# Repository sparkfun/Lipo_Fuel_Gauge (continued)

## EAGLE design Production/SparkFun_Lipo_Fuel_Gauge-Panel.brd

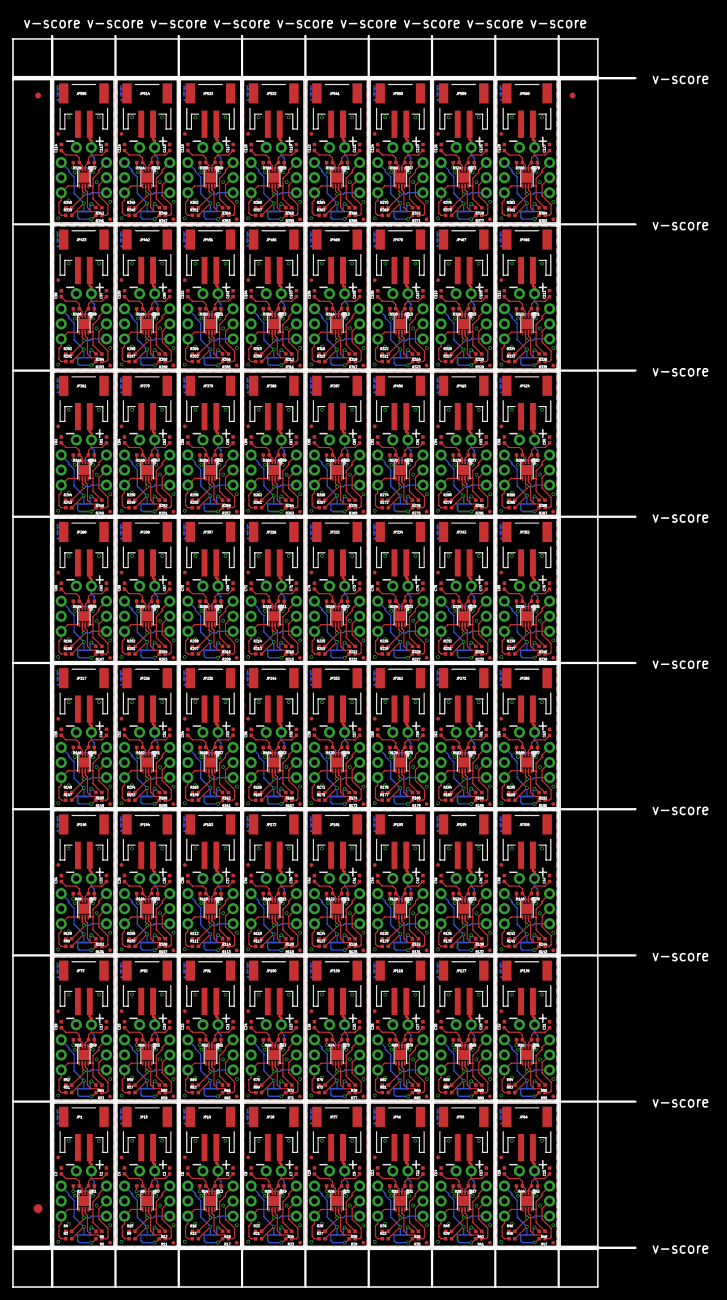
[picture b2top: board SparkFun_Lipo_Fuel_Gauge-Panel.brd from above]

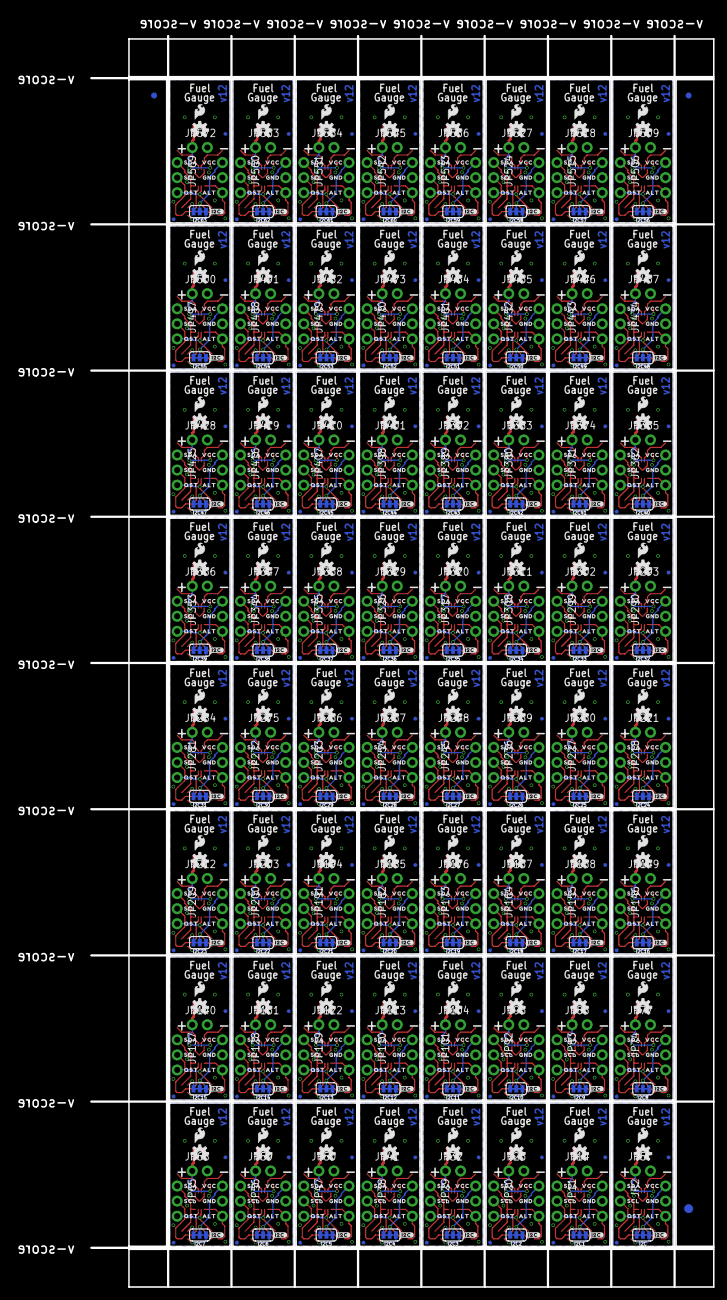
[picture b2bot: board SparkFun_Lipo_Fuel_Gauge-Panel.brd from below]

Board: 2 copper layers, 104.9 x 210.8 mm, 1798 parts (963 on the bottom side), 704 nets.

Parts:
C1, C3, C5, C7, C9, C11, C13, C15, C17, C19, C21, C23, C25, C27, C29, C31, C33, C35, C37, C39, C41, C43, C45, C47, C49, C51, C53, C55, C57, C59, C61, C63, C65, C67, C69, C71, C73, C75, C77, C79, C81, C83, C85, C87, C89, C91, C93, C95, C97, C99, C101, C103, C105, C107, C109, C111, C113, C115, C117, C119, C121, C123, C125, C127: 1.0uF; 0402-TIGHT
C2, C4, C6, C8, C10, C12, C14, C16, C18, C20, C22, C24, C26, C28, C30, C32, C34, C36, C38, C40, C42, C44, C46, C48, C50, C52, C54, C56, C58, C60, C62, C64, C66, C68, C70, C72, C74, C76, C78, C80, C82, C84, C86, C88, C90, C92, C94, C96, C98, C100, C102, C104, C106, C108, C110, C112, C114, C116, C118, C120, C122, C124, C126, C128: 10nF; 0402-TIGHT
E$1, E$2, E$3, E$4: FIDUCIAL-1X2
E$5, E$6: FIDUCIAL-1.5X3
I2C, I2C1, I2C2, I2C3, I2C4, I2C5, I2C6, I2C7, I2C8, I2C9, I2C10, I2C11, I2C12, I2C13, I2C14, I2C15, I2C16, I2C17, I2C18, I2C19, I2C20, I2C21, I2C22, I2C23, I2C24, I2C25, I2C26, I2C27, I2C28, I2C29, I2C30, I2C31, I2C32, I2C33, I2C34, I2C35, I2C36, I2C37, I2C38, I2C39, I2C40, I2C41, I2C42, I2C43, I2C44, I2C45, I2C46, I2C47, I2C48, I2C49, I2C50, I2C51, I2C52, I2C53, I2C54, I2C55, I2C56, I2C57, I2C58, I2C59, I2C60, I2C61, I2C62, I2C63: JUMPER-SMT_3_2-NC_TRACE_SILK; SMT-JUMPER_3_2-NC_TRACE_SILK
JP1, JP10, JP19, JP28, JP37, JP46, JP55, JP64, JP73, JP82, JP91, JP100, JP109, JP118, JP127, JP136, JP145, JP154, JP163, JP172, JP181, JP190, JP199, JP208, JP217, JP226, JP235, JP244, JP253, JP262, JP271, JP280, JP289, JP298, JP307, JP316, JP325, JP334, JP343, JP352, JP361, JP370, JP379, JP388, JP397, JP406, JP415, JP424, JP433, JP442, JP451, JP460, JP469, JP478, JP487, JP496, JP505, JP514, JP523, JP532, JP541, JP550, JP559, JP568: input; JST-2-SMD
JP2, JP4, JP11, JP12, JP20, JP21, JP29, JP30, JP38, JP39, JP47, JP48, JP56, JP57, JP65, JP66, JP74, JP75, JP83, JP84, JP92, JP93, JP101, JP102, JP110, JP111, JP119, JP120, JP128, JP129, JP137, JP138, JP146, JP147, JP155, JP156, JP164, JP165, JP173, JP174, JP182, JP183, JP191, JP192, JP200, JP201, JP209, JP210, JP218, JP219, JP227, JP228, JP236, JP237, JP245, JP246, JP254, JP255, JP263, JP264, JP272, JP273, JP281, JP282, JP290, JP291, JP299, JP300, JP308, JP309, JP317, JP318, JP326, JP327, JP335, JP336, JP344, JP345, JP353, JP354, JP362, JP363, JP371, JP372, JP380, JP381, JP389, JP390, JP398, JP399, JP407, JP408, JP416, JP417, JP425, JP426, JP434, JP435, JP443, JP444, JP452, JP453, JP461, JP462, JP470, JP471, JP479, JP480, JP488, JP489, JP497, JP498, JP506, JP507, JP515, JP516, JP524, JP525, JP533, JP534, JP542, JP543, JP551, JP552, JP560, JP561, JP569, JP570: 1X03_NO_SILK
JP3, JP13, JP22, JP31, JP40, JP49, JP58, JP67, JP76, JP85, JP94, JP103, JP112, JP121, JP130, JP139, JP148, JP157, JP166, JP175, JP184, JP193, JP202, JP211, JP220, JP229, JP238, JP247, JP256, JP265, JP274, JP283, JP292, JP301, JP310, JP319, JP328, JP337, JP346, JP355, JP364, JP373, JP382, JP391, JP400, JP409, JP418, JP427, JP436, JP445, JP454, JP463, JP472, JP481, JP490, JP499, JP508, JP517, JP526, JP535, JP544, JP553, JP562, JP571: SFE_LOGO_FLAME.1_INCH; SFE_LOGO_FLAME_.1
JP5, JP14, JP23, JP32, JP41, JP50, JP59, JP68, JP77, JP86, JP95, JP104, JP113, JP122, JP131, JP140, JP149, JP158, JP167, JP176, JP185, JP194, JP203, JP212, JP221, JP230, JP239, JP248, JP257, JP266, JP275, JP284, JP293, JP302, JP311, JP320, JP329, JP338, JP347, JP356, JP365, JP374, JP383, JP392, JP401, JP410, JP419, JP428, JP437, JP446, JP455, JP464, JP473, JP482, JP491, JP500, JP509, JP518, JP527, JP536, JP545, JP554, JP563, JP572: 1X02_NO_SILK
JP6, JP7, JP8, JP9, JP15, JP16, JP17, JP18, JP24, JP25, JP26, JP27, JP33, JP34, JP35, JP36, JP42, JP43, JP44, JP45, JP51, JP52, JP53, JP54, JP60, JP61, JP62, JP63, JP69, JP70, JP71, JP72, JP78, JP79, JP80, JP81, JP87, JP88, JP89, JP90, JP96, JP97, JP98, JP99, JP105, JP106, JP107, JP108, JP114, JP115, JP116, JP117, JP123, JP124, JP125, JP126, JP132, JP133, JP134, JP135, JP141, JP142, JP143, JP144, JP150, JP151, JP152, JP153, JP159, JP160, JP161, JP162, JP168, JP169, JP170, JP171, JP177, JP178, JP179, JP180, JP186, JP187, JP188, JP189, JP195, JP196, JP197, JP198, JP204, JP205, JP206, JP207, JP213, JP214, JP215, JP216, JP222, JP223, JP224, JP225, JP231, JP232, JP233, JP234, JP240, JP241, JP242, JP243, JP249, JP250, JP251, JP252, JP258, JP259, JP260, JP261, JP267, JP268, JP269, JP270, JP276, JP277, JP278, JP279, JP285, JP286, JP287, JP288, JP294, JP295, JP296, JP297, JP303, JP304, JP305, JP306, JP312, JP313, JP314, JP315, JP321, JP322, JP323, JP324, JP330, JP331, JP332, JP333, JP339, JP340, JP341, JP342, JP348, JP349, JP350, JP351, JP357, JP358, JP359, JP360, JP366, JP367, JP368, JP369, JP375, JP376, JP377, JP378, JP384, JP385, JP386, JP387, JP393, JP394, JP395, JP396, JP402, JP403, JP404, JP405, JP411, JP412, JP413, JP414, JP420, JP421, JP422, JP423, JP429, JP430, JP431, JP432, JP438, JP439, JP440, JP441, JP447, JP448, JP449, JP450, JP456, JP457, JP458, JP459, JP465, JP466, JP467, JP468, JP474, JP475, JP476, JP477, JP483, JP484, JP485, JP486, JP492, JP493, JP494, JP495, JP501, JP502, JP503, JP504, JP510, JP511, JP512, JP513, JP519, JP520, JP521, JP522, JP528, JP529, JP530, JP531, JP537, JP538, JP539, JP540, JP546, JP547, JP548, JP549, JP555, JP556, JP557, JP558, JP564, JP565, JP566, JP567, JP573, JP574, JP575, JP576: FIDUCIALUFIDUCIAL; FIDUCIAL-MICRO
LOGO1, LOGO2, LOGO3, LOGO4, LOGO5, LOGO6, LOGO7, LOGO8, LOGO9, LOGO10, LOGO11, LOGO12, LOGO13, LOGO14, LOGO15, LOGO16, LOGO17, LOGO18, LOGO19, LOGO20, LOGO21, LOGO22, LOGO23, LOGO24, LOGO25, LOGO26, LOGO27, LOGO28, LOGO29, LOGO30, LOGO31, LOGO32, LOGO33, LOGO34, LOGO35, LOGO36, LOGO37, LOGO38, LOGO39, LOGO40, LOGO41, LOGO42, LOGO43, LOGO44, LOGO45, LOGO46, LOGO47, LOGO48, LOGO49, LOGO50, LOGO51, LOGO52, LOGO53, LOGO54, LOGO55, LOGO56, LOGO57, LOGO58, LOGO59, LOGO60, LOGO61, LOGO62, LOGO63, LOGO64: SFE_LOGO_NAME_FLAMEBLANK; BLANK
R1, R7, R13, R19, R25, R31, R37, R43, R49, R55, R61, R67, R73, R79, R85, R91, R97, R103, R109, R115, R121, R127, R133, R139, R145, R151, R157, R163, R169, R175, R181, R187, R193, R199, R205, R211, R217, R223, R229, R235, R241, R247, R253, R259, R265, R271, R277, R283, R289, R295, R301, R307, R313, R319, R325, R331, R337, R343, R349, R355, R361, R367, R373, R379: 1k; 0402-TIGHT
R2, R8, R14, R20, R26, R32, R38, R44, R50, R56, R62, R68, R74, R80, R86, R92, R98, R104, R110, R116, R122, R128, R134, R140, R146, R152, R158, R164, R170, R176, R182, R188, R194, R200, R206, R212, R218, R224, R230, R236, R242, R248, R254, R260, R266, R272, R278, R284, R290, R296, R302, R308, R314, R320, R326, R332, R338, R344, R350, R356, R362, R368, R374, R380: 100; 0402-TIGHT
R3, R4, R5, R6, R9, R10, R11, R12, R15, R16, R17, R18, R21, R22, R23, R24, R27, R28, R29, R30, R33, R34, R35, R36, R39, R40, R41, R42, R45, R46, R47, R48, R51, R52, R53, R54, R57, R58, R59, R60, R63, R64, R65, R66, R69, R70, R71, R72, R75, R76, R77, R78, R81, R82, R83, R84, R87, R88, R89, R90, R93, R94, R95, R96, R99, R100, R101, R102, R105, R106, R107, R108, R111, R112, R113, R114, R117, R118, R119, R120, R123, R124, R125, R126, R129, R130, R131, R132, R135, R136, R137, R138, R141, R142, R143, R144, R147, R148, R149, R150, R153, R154, R155, R156, R159, R160, R161, R162, R165, R166, R167, R168, R171, R172, R173, R174, R177, R178, R179, R180, R183, R184, R185, R186, R189, R190, R191, R192, R195, R196, R197, R198, R201, R202, R203, R204, R207, R208, R209, R210, R213, R214, R215, R216, R219, R220, R221, R222, R225, R226, R227, R228, R231, R232, R233, R234, R237, R238, R239, R240, R243, R244, R245, R246, R249, R250, R251, R252, R255, R256, R257, R258, R261, R262, R263, R264, R267, R268, R269, R270, R273, R274, R275, R276, R279, R280, R281, R282, R285, R286, R287, R288, R291, R292, R293, R294, R297, R298, R299, R300, R303, R304, R305, R306, R309, R310, R311, R312, R315, R316, R317, R318, R321, R322, R323, R324, R327, R328, R329, R330, R333, R334, R335, R336, R339, R340, R341, R342, R345, R346, R347, R348, R351, R352, R353, R354, R357, R358, R359, R360, R363, R364, R365, R366, R369, R370, R371, R372, R375, R376, R377, R378, R381, R382, R383, R384: 2.2k; 0402-TIGHT
U1, U2, U3, U4, U5, U6, U7, U8, U9, U10, U11, U12, U13, U14, U15, U16, U17, U18, U19, U20, U21, U22, U23, U24, U25, U26, U27, U28, U29, U30, U31, U32, U33, U34, U35, U36, U37, U38, U39, U40, U41, U42, U43, U44, U45, U46, U47, U48, U49, U50, U51, U52, U53, U54, U55, U56, U57, U58, U59, U60, U61, U62, U63, U64: MAX1704X; TDFN-8
U$1, U$9, U$17, U$25, U$33, U$41, U$49, U$57, U$65, U$73, U$81, U$89, U$97, U$105, U$113, U$121, U$129, U$137, U$145, U$153, U$161, U$169, U$177, U$185, U$193, U$201, U$209, U$217, U$225, U$233, U$241, U$249, U$257, U$265, U$273, U$281, U$289, U$297, U$305, U$313, U$321, U$329, U$337, U$345, U$353, U$361, U$369, U$377, U$385, U$393, U$401, U$409, U$417, U$425, U$433, U$441, U$449, U$457, U$465, U$473, U$481, U$489, U$497, U$505: OSHW-LOGOS; OSHW-LOGO-S
U$2, U$11, U$19, U$27, U$35, U$43, U$51, U$59, U$67, U$75, U$83, U$91, U$99, U$107, U$115, U$123, U$131, U$139, U$147, U$155, U$163, U$171, U$179, U$187, U$195, U$203, U$211, U$219, U$227, U$235, U$243, U$251, U$259, U$267, U$275, U$283, U$291, U$299, U$307, U$315, U$323, U$331, U$339, U$347, U$355, U$363, U$371, U$379, U$387, U$395, U$403, U$411, U$419, U$427, U$435, U$443, U$451, U$459, U$467, U$475, U$483, U$491, U$499, U$507: SDA0
U$3, U$12, U$20, U$28, U$36, U$44, U$52, U$60, U$68, U$76, U$84, U$92, U$100, U$108, U$116, U$124, U$132, U$140, U$148, U$156, U$164, U$172, U$180, U$188, U$196, U$204, U$212, U$220, U$228, U$236, U$244, U$252, U$260, U$268, U$276, U$284, U$292, U$300, U$308, U$316, U$324, U$332, U$340, U$348, U$356, U$364, U$372, U$380, U$388, U$396, U$404, U$412, U$420, U$428, U$436, U$444, U$452, U$460, U$468, U$476, U$484, U$492, U$500, U$508: SCL0
U$4, U$13, U$21, U$29, U$37, U$45, U$53, U$61, U$69, U$77, U$85, U$93, U$101, U$109, U$117, U$125, U$133, U$141, U$149, U$157, U$165, U$173, U$181, U$189, U$197, U$205, U$213, U$221, U$229, U$237, U$245, U$253, U$261, U$269, U$277, U$285, U$293, U$301, U$309, U$317, U$325, U$333, U$341, U$349, U$357, U$365, U$373, U$381, U$389, U$397, U$405, U$413, U$421, U$429, U$437, U$445, U$453, U$461, U$469, U$477, U$485, U$493, U$501, U$509: QST0
U$5, U$14, U$22, U$30, U$38, U$46, U$54, U$62, U$70, U$78, U$86, U$94, U$102, U$110, U$118, U$126, U$134, U$142, U$150, U$158, U$166, U$174, U$182, U$190, U$198, U$206, U$214, U$222, U$230, U$238, U$246, U$254, U$262, U$270, U$278, U$286, U$294, U$302, U$310, U$318, U$326, U$334, U$342, U$350, U$358, U$366, U$374, U$382, U$390, U$398, U$406, U$414, U$422, U$430, U$438, U$446, U$454, U$462, U$470, U$478, U$486, U$494, U$502, U$510: VCC0
U$6, U$15, U$23, U$31, U$39, U$47, U$55, U$63, U$71, U$79, U$87, U$95, U$103, U$111, U$119, U$127, U$135, U$143, U$151, U$159, U$167, U$175, U$183, U$191, U$199, U$207, U$215, U$223, U$231, U$239, U$247, U$255, U$263, U$271, U$279, U$287, U$295, U$303, U$311, U$319, U$327, U$335, U$343, U$351, U$359, U$367, U$375, U$383, U$391, U$399, U$407, U$415, U$423, U$431, U$439, U$447, U$455, U$463, U$471, U$479, U$487, U$495, U$503, U$511: GND0
U$7, U$16, U$24, U$32, U$40, U$48, U$56, U$64, U$72, U$80, U$88, U$96, U$104, U$112, U$120, U$128, U$136, U$144, U$152, U$160, U$168, U$176, U$184, U$192, U$200, U$208, U$216, U$224, U$232, U$240, U$248, U$256, U$264, U$272, U$280, U$288, U$296, U$304, U$312, U$320, U$328, U$336, U$344, U$352, U$360, U$368, U$376, U$384, U$392, U$400, U$408, U$416, U$424, U$432, U$440, U$448, U$456, U$464, U$472, U$480, U$488, U$496, U$504, U$512: ALT0
U$8, U$10, U$18, U$26, U$34, U$42, U$50, U$58, U$66, U$74, U$82, U$90, U$98, U$106, U$114, U$122, U$130, U$138, U$146, U$154, U$162, U$170, U$178, U$186, U$194, U$202, U$210, U$218, U$226, U$234, U$242, U$250, U$258, U$266, U$274, U$282, U$290, U$298, U$306, U$314, U$322, U$330, U$338, U$346, U$354, U$362, U$370, U$378, U$386, U$394, U$402, U$410, U$418, U$426, U$434, U$442, U$450, U$458, U$466, U$474, U$482, U$490, U$498, U$506: #I2C#0

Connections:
ALT: JP4.3, R3.1, U2.5
ALT1: JP12.3, R9.1, U1.5
ALT2: JP21.3, R15.1, U3.5
ALT3: JP30.3, R21.1, U4.5
ALT4: JP39.3, R27.1, U5.5
ALT5: JP48.3, R33.1, U6.5
ALT6: JP57.3, R39.1, U7.5
ALT7: JP66.3, R45.1, U8.5
ALT8: JP75.3, R51.1, U9.5
ALT9: JP84.3, R57.1, U10.5
ALT10: JP93.3, R63.1, U11.5
ALT11: JP102.3, R69.1, U12.5
ALT12: JP111.3, R75.1, U13.5
ALT13: JP120.3, R81.1, U14.5
ALT14: JP129.3, R87.1, U15.5
ALT15: JP138.3, R93.1, U16.5
ALT16: JP147.3, R99.1, U17.5
ALT17: JP156.3, R105.1, U18.5
ALT18: JP165.3, R111.1, U19.5
ALT19: JP174.3, R117.1, U20.5
ALT20: JP183.3, R123.1, U21.5
ALT21: JP192.3, R129.1, U22.5
ALT22: JP201.3, R135.1, U23.5
ALT23: JP210.3, R141.1, U24.5
ALT24: JP219.3, R147.1, U25.5
ALT25: JP228.3, R153.1, U26.5
ALT26: JP237.3, R159.1, U27.5
ALT27: JP246.3, R165.1, U28.5
ALT28: JP255.3, R171.1, U29.5
ALT29: JP264.3, R177.1, U30.5
ALT30: JP273.3, R183.1, U31.5
ALT31: JP282.3, R189.1, U32.5
ALT32: JP291.3, R195.1, U33.5
ALT33: JP300.3, R201.1, U34.5
ALT34: JP309.3, R207.1, U35.5
ALT35: JP318.3, R213.1, U36.5
ALT36: JP327.3, R219.1, U37.5
ALT37: JP336.3, R225.1, U38.5
ALT38: JP345.3, R231.1, U39.5
ALT39: JP354.3, R237.1, U40.5
ALT40: JP363.3, R243.1, U41.5
ALT41: JP372.3, R249.1, U42.5
ALT42: JP381.3, R255.1, U43.5
ALT43: JP390.3, R261.1, U44.5
ALT44: JP399.3, R267.1, U45.5
ALT45: JP408.3, R273.1, U46.5
ALT46: JP417.3, R279.1, U47.5
ALT47: JP426.3, R285.1, U48.5
ALT48: JP435.3, R291.1, U49.5
ALT49: JP444.3, R297.1, U50.5
ALT50: JP453.3, R303.1, U51.5
ALT51: JP462.3, R309.1, U52.5
ALT52: JP471.3, R315.1, U53.5
ALT53: JP480.3, R321.1, U54.5
ALT54: JP489.3, R327.1, U55.5
ALT55: JP498.3, R333.1, U56.5
ALT56: JP507.3, R339.1, U57.5
ALT57: JP516.3, R345.1, U58.5
ALT58: JP525.3, R351.1, U59.5
ALT59: JP534.3, R357.1, U60.5
ALT60: JP543.3, R363.1, U61.5
ALT61: JP552.3, R369.1, U62.5
ALT62: JP561.3, R375.1, U63.5
ALT63: JP570.3, R381.1, U64.5
GND: C1.2, C2.2, JP1.1, JP4.2, JP5.2, R4.1, U2.1, U2.4, U2.EP
GND1: C3.2, C4.2, JP10.1, JP12.2, JP14.2, R10.1, U1.1, U1.4, U1.EP
GND2: C5.2, C6.2, JP19.1, JP21.2, JP23.2, R16.1, U3.1, U3.4, U3.EP
GND3: C7.2, C8.2, JP28.1, JP30.2, JP32.2, R22.1, U4.1, U4.4, U4.EP
GND4: C9.2, C10.2, JP37.1, JP39.2, JP41.2, R28.1, U5.1, U5.4, U5.EP
GND5: C11.2, C12.2, JP46.1, JP48.2, JP50.2, R34.1, U6.1, U6.4, U6.EP
GND6: C13.2, C14.2, JP55.1, JP57.2, JP59.2, R40.1, U7.1, U7.4, U7.EP
GND7: C15.2, C16.2, JP64.1, JP66.2, JP68.2, R46.1, U8.1, U8.4, U8.EP
GND8: C17.2, C18.2, JP73.1, JP75.2, JP77.2, R52.1, U9.1, U9.4, U9.EP
GND9: C19.2, C20.2, JP82.1, JP84.2, JP86.2, R58.1, U10.1, U10.4, U10.EP
GND10: C21.2, C22.2, JP91.1, JP93.2, JP95.2, R64.1, U11.1, U11.4, U11.EP
GND11: C23.2, C24.2, JP100.1, JP102.2, JP104.2, R70.1, U12.1, U12.4, U12.EP
GND12: C25.2, C26.2, JP109.1, JP111.2, JP113.2, R76.1, U13.1, U13.4, U13.EP
GND13: C27.2, C28.2, JP118.1, JP120.2, JP122.2, R82.1, U14.1, U14.4, U14.EP
GND14: C29.2, C30.2, JP127.1, JP129.2, JP131.2, R88.1, U15.1, U15.4, U15.EP
GND15: C31.2, C32.2, JP136.1, JP138.2, JP140.2, R94.1, U16.1, U16.4, U16.EP
GND16: C33.2, C34.2, JP145.1, JP147.2, JP149.2, R100.1, U17.1, U17.4, U17.EP
GND17: C35.2, C36.2, JP154.1, JP156.2, JP158.2, R106.1, U18.1, U18.4, U18.EP
GND18: C37.2, C38.2, JP163.1, JP165.2, JP167.2, R112.1, U19.1, U19.4, U19.EP
GND19: C39.2, C40.2, JP172.1, JP174.2, JP176.2, R118.1, U20.1, U20.4, U20.EP
GND20: C41.2, C42.2, JP181.1, JP183.2, JP185.2, R124.1, U21.1, U21.4, U21.EP
GND21: C43.2, C44.2, JP190.1, JP192.2, JP194.2, R130.1, U22.1, U22.4, U22.EP
GND22: C45.2, C46.2, JP199.1, JP201.2, JP203.2, R136.1, U23.1, U23.4, U23.EP
GND23: C47.2, C48.2, JP208.1, JP210.2, JP212.2, R142.1, U24.1, U24.4, U24.EP
GND24: C49.2, C50.2, JP217.1, JP219.2, JP221.2, R148.1, U25.1, U25.4, U25.EP
GND25: C51.2, C52.2, JP226.1, JP228.2, JP230.2, R154.1, U26.1, U26.4, U26.EP
GND26: C53.2, C54.2, JP235.1, JP237.2, JP239.2, R160.1, U27.1, U27.4, U27.EP
GND27: C55.2, C56.2, JP244.1, JP246.2, JP248.2, R166.1, U28.1, U28.4, U28.EP
GND28: C57.2, C58.2, JP253.1, JP255.2, JP257.2, R172.1, U29.1, U29.4, U29.EP
GND29: C59.2, C60.2, JP262.1, JP264.2, JP266.2, R178.1, U30.1, U30.4, U30.EP
GND30: C61.2, C62.2, JP271.1, JP273.2, JP275.2, R184.1, U31.1, U31.4, U31.EP
GND31: C63.2, C64.2, JP280.1, JP282.2, JP284.2, R190.1, U32.1, U32.4, U32.EP
GND32: C65.2, C66.2, JP289.1, JP291.2, JP293.2, R196.1, U33.1, U33.4, U33.EP
GND33: C67.2, C68.2, JP298.1, JP300.2, JP302.2, R202.1, U34.1, U34.4, U34.EP
GND34: C69.2, C70.2, JP307.1, JP309.2, JP311.2, R208.1, U35.1, U35.4, U35.EP
GND35: C71.2, C72.2, JP316.1, JP318.2, JP320.2, R214.1, U36.1, U36.4, U36.EP
GND36: C73.2, C74.2, JP325.1, JP327.2, JP329.2, R220.1, U37.1, U37.4, U37.EP
GND37: C75.2, C76.2, JP334.1, JP336.2, JP338.2, R226.1, U38.1, U38.4, U38.EP
GND38: C77.2, C78.2, JP343.1, JP345.2, JP347.2, R232.1, U39.1, U39.4, U39.EP
GND39: C79.2, C80.2, JP352.1, JP354.2, JP356.2, R238.1, U40.1, U40.4, U40.EP
GND40: C81.2, C82.2, JP361.1, JP363.2, JP365.2, R244.1, U41.1, U41.4, U41.EP
GND41: C83.2, C84.2, JP370.1, JP372.2, JP374.2, R250.1, U42.1, U42.4, U42.EP
GND42: C85.2, C86.2, JP379.1, JP381.2, JP383.2, R256.1, U43.1, U43.4, U43.EP
GND43: C87.2, C88.2, JP388.1, JP390.2, JP392.2, R262.1, U44.1, U44.4, U44.EP
GND44: C89.2, C90.2, JP397.1, JP399.2, JP401.2, R268.1, U45.1, U45.4, U45.EP
GND45: C91.2, C92.2, JP406.1, JP408.2, JP410.2, R274.1, U46.1, U46.4, U46.EP
GND46: C93.2, C94.2, JP415.1, JP417.2, JP419.2, R280.1, U47.1, U47.4, U47.EP
GND47: C95.2, C96.2, JP424.1, JP426.2, JP428.2, R286.1, U48.1, U48.4, U48.EP
GND48: C97.2, C98.2, JP433.1, JP435.2, JP437.2, R292.1, U49.1, U49.4, U49.EP
GND49: C99.2, C100.2, JP442.1, JP444.2, JP446.2, R298.1, U50.1, U50.4, U50.EP
GND50: C101.2, C102.2, JP451.1, JP453.2, JP455.2, R304.1, U51.1, U51.4, U51.EP
GND51: C103.2, C104.2, JP460.1, JP462.2, JP464.2, R310.1, U52.1, U52.4, U52.EP
GND52: C105.2, C106.2, JP469.1, JP471.2, JP473.2, R316.1, U53.1, U53.4, U53.EP
GND53: C107.2, C108.2, JP478.1, JP480.2, JP482.2, R322.1, U54.1, U54.4, U54.EP
GND54: C109.2, C110.2, JP487.1, JP489.2, JP491.2, R328.1, U55.1, U55.4, U55.EP
GND55: C111.2, C112.2, JP496.1, JP498.2, JP500.2, R334.1, U56.1, U56.4, U56.EP
GND56: C113.2, C114.2, JP505.1, JP507.2, JP509.2, R340.1, U57.1, U57.4, U57.EP
GND57: C115.2, C116.2, JP514.1, JP516.2, JP518.2, R346.1, U58.1, U58.4, U58.EP
GND58: C117.2, C118.2, JP523.1, JP525.2, JP527.2, R352.1, U59.1, U59.4, U59.EP
GND59: C119.2, C120.2, JP532.1, JP534.2, JP536.2, R358.1, U60.1, U60.4, U60.EP
GND60: C121.2, C122.2, JP541.1, JP543.2, JP545.2, R364.1, U61.1, U61.4, U61.EP
GND61: C123.2, C124.2, JP550.1, JP552.2, JP554.2, R370.1, U62.1, U62.4, U62.EP
GND62: C125.2, C126.2, JP559.1, JP561.2, JP563.2, R376.1, U63.1, U63.4, U63.EP
GND63: C127.2, C128.2, JP568.1, JP570.2, JP572.2, R382.1, U64.1, U64.4, U64.EP
unnamed: I2C.3, R6.2
unnamed: C1.1, R1.2, U2.2
unnamed: I2C.1, R5.2
unnamed: C3.1, R7.2, U1.2
unnamed: I2C1.3, R12.2
unnamed: I2C1.1, R11.2
unnamed: C5.1, R13.2, U3.2
unnamed: I2C2.3, R18.2
unnamed: I2C2.1, R17.2
unnamed: C7.1, R19.2, U4.2
unnamed: I2C3.3, R24.2
unnamed: I2C3.1, R23.2
unnamed: C9.1, R25.2, U5.2
unnamed: I2C4.3, R30.2
unnamed: I2C4.1, R29.2
unnamed: C11.1, R31.2, U6.2
unnamed: I2C5.3, R36.2
unnamed: I2C5.1, R35.2
unnamed: C13.1, R37.2, U7.2
unnamed: I2C6.3, R42.2
unnamed: I2C6.1, R41.2
unnamed: C15.1, R43.2, U8.2
unnamed: I2C7.3, R48.2
unnamed: I2C7.1, R47.2
unnamed: C17.1, R49.2, U9.2
unnamed: I2C8.3, R54.2
unnamed: I2C8.1, R53.2
unnamed: C19.1, R55.2, U10.2
unnamed: I2C9.3, R60.2
unnamed: I2C9.1, R59.2
unnamed: C21.1, R61.2, U11.2
unnamed: I2C10.3, R66.2
unnamed: I2C10.1, R65.2
unnamed: C23.1, R67.2, U12.2
unnamed: I2C11.3, R72.2
unnamed: I2C11.1, R71.2
unnamed: C25.1, R73.2, U13.2
unnamed: I2C12.3, R78.2
unnamed: I2C12.1, R77.2
unnamed: C27.1, R79.2, U14.2
unnamed: I2C13.3, R84.2
unnamed: I2C13.1, R83.2
unnamed: C29.1, R85.2, U15.2
unnamed: I2C14.3, R90.2
unnamed: I2C14.1, R89.2
unnamed: C31.1, R91.2, U16.2
unnamed: I2C15.3, R96.2
unnamed: I2C15.1, R95.2
unnamed: C33.1, R97.2, U17.2
unnamed: I2C16.3, R102.2
unnamed: I2C16.1, R101.2
unnamed: C35.1, R103.2, U18.2
unnamed: I2C17.3, R108.2
unnamed: I2C17.1, R107.2
unnamed: C37.1, R109.2, U19.2
unnamed: I2C18.3, R114.2
unnamed: I2C18.1, R113.2
unnamed: C39.1, R115.2, U20.2
unnamed: I2C19.3, R120.2
unnamed: I2C19.1, R119.2
unnamed: C41.1, R121.2, U21.2
unnamed: I2C20.3, R126.2
unnamed: I2C20.1, R125.2
unnamed: C43.1, R127.2, U22.2
unnamed: I2C21.3, R132.2
unnamed: I2C21.1, R131.2
unnamed: C45.1, R133.2, U23.2
unnamed: I2C22.3, R138.2
unnamed: I2C22.1, R137.2
unnamed: C47.1, R139.2, U24.2
unnamed: I2C23.3, R144.2
unnamed: I2C23.1, R143.2
unnamed: C49.1, R145.2, U25.2
unnamed: I2C24.3, R150.2
unnamed: I2C24.1, R149.2
unnamed: C51.1, R151.2, U26.2
unnamed: I2C25.3, R156.2
unnamed: I2C25.1, R155.2
unnamed: C53.1, R157.2, U27.2
unnamed: I2C26.3, R162.2
unnamed: I2C26.1, R161.2
unnamed: C55.1, R163.2, U28.2
unnamed: I2C27.3, R168.2
unnamed: I2C27.1, R167.2
unnamed: C57.1, R169.2, U29.2
unnamed: I2C28.3, R174.2
unnamed: I2C28.1, R173.2
unnamed: C59.1, R175.2, U30.2
unnamed: I2C29.3, R180.2
unnamed: I2C29.1, R179.2
unnamed: C61.1, R181.2, U31.2
unnamed: I2C30.3, R186.2
unnamed: I2C30.1, R185.2
unnamed: C63.1, R187.2, U32.2
unnamed: I2C31.3, R192.2
unnamed: I2C31.1, R191.2
unnamed: C65.1, R193.2, U33.2
unnamed: I2C32.3, R198.2
unnamed: I2C32.1, R197.2
unnamed: C67.1, R199.2, U34.2
unnamed: I2C33.3, R204.2
unnamed: I2C33.1, R203.2
unnamed: C69.1, R205.2, U35.2
unnamed: I2C34.3, R210.2
unnamed: I2C34.1, R209.2
unnamed: C71.1, R211.2, U36.2
unnamed: I2C35.3, R216.2
unnamed: I2C35.1, R215.2
unnamed: C73.1, R217.2, U37.2
unnamed: I2C36.3, R222.2
unnamed: I2C36.1, R221.2
unnamed: C75.1, R223.2, U38.2
unnamed: I2C37.3, R228.2
unnamed: I2C37.1, R227.2
unnamed: C77.1, R229.2, U39.2
unnamed: I2C38.3, R234.2
unnamed: I2C38.1, R233.2
unnamed: C79.1, R235.2, U40.2
unnamed: I2C39.3, R240.2
unnamed: I2C39.1, R239.2
unnamed: C81.1, R241.2, U41.2
unnamed: I2C40.3, R246.2
unnamed: I2C40.1, R245.2
unnamed: C83.1, R247.2, U42.2
unnamed: I2C41.3, R252.2
unnamed: I2C41.1, R251.2
unnamed: C85.1, R253.2, U43.2
unnamed: I2C42.3, R258.2
unnamed: I2C42.1, R257.2
unnamed: C87.1, R259.2, U44.2
unnamed: I2C43.3, R264.2
unnamed: I2C43.1, R263.2
unnamed: C89.1, R265.2, U45.2
unnamed: I2C44.3, R270.2
unnamed: I2C44.1, R269.2
unnamed: C91.1, R271.2, U46.2
unnamed: I2C45.3, R276.2
unnamed: I2C45.1, R275.2
unnamed: C93.1, R277.2, U47.2
unnamed: I2C46.3, R282.2
unnamed: I2C46.1, R281.2
unnamed: C95.1, R283.2, U48.2
unnamed: I2C47.3, R288.2
unnamed: I2C47.1, R287.2
unnamed: C97.1, R289.2, U49.2
unnamed: I2C48.3, R294.2
unnamed: I2C48.1, R293.2
unnamed: C99.1, R295.2, U50.2
unnamed: I2C49.3, R300.2
unnamed: I2C49.1, R299.2
unnamed: C101.1, R301.2, U51.2
unnamed: I2C50.3, R306.2
unnamed: I2C50.1, R305.2
unnamed: C103.1, R307.2, U52.2
unnamed: I2C51.3, R312.2
unnamed: I2C51.1, R311.2
unnamed: C105.1, R313.2, U53.2
unnamed: I2C52.3, R318.2
unnamed: I2C52.1, R317.2
unnamed: C107.1, R319.2, U54.2
unnamed: I2C53.3, R324.2
unnamed: I2C53.1, R323.2
unnamed: C109.1, R325.2, U55.2
unnamed: I2C54.3, R330.2
unnamed: I2C54.1, R329.2
unnamed: C111.1, R331.2, U56.2
unnamed: I2C55.3, R336.2
unnamed: I2C55.1, R335.2
unnamed: C113.1, R337.2, U57.2
unnamed: I2C56.3, R342.2
unnamed: I2C56.1, R341.2
unnamed: C115.1, R343.2, U58.2
unnamed: I2C57.3, R348.2
unnamed: I2C57.1, R347.2
unnamed: C117.1, R349.2, U59.2
unnamed: I2C58.3, R354.2
unnamed: I2C58.1, R353.2
unnamed: C119.1, R355.2, U60.2
unnamed: I2C59.3, R360.2
unnamed: I2C59.1, R359.2
unnamed: C121.1, R361.2, U61.2
unnamed: I2C60.3, R366.2
unnamed: I2C60.1, R365.2
unnamed: C123.1, R367.2, U62.2
unnamed: I2C61.3, R372.2
unnamed: I2C61.1, R371.2
unnamed: C125.1, R373.2, U63.2
unnamed: I2C62.3, R378.2
unnamed: I2C62.1, R377.2
unnamed: C127.1, R379.2, U64.2
unnamed: I2C63.3, R384.2
unnamed: I2C63.1, R383.2
QST: JP2.3, R4.2, U2.6
QST1: JP11.3, R10.2, U1.6
QST2: JP20.3, R16.2, U3.6
QST3: JP29.3, R22.2, U4.6
QST4: JP38.3, R28.2, U5.6
QST5: JP47.3, R34.2, U6.6
QST6: JP56.3, R40.2, U7.6
QST7: JP65.3, R46.2, U8.6
QST8: JP74.3, R52.2, U9.6
QST9: JP83.3, R58.2, U10.6
QST10: JP92.3, R64.2, U11.6
QST11: JP101.3, R70.2, U12.6
QST12: JP110.3, R76.2, U13.6
QST13: JP119.3, R82.2, U14.6
QST14: JP128.3, R88.2, U15.6
QST15: JP137.3, R94.2, U16.6
QST16: JP146.3, R100.2, U17.6
QST17: JP155.3, R106.2, U18.6
QST18: JP164.3, R112.2, U19.6
QST19: JP173.3, R118.2, U20.6
QST20: JP182.3, R124.2, U21.6
QST21: JP191.3, R130.2, U22.6
QST22: JP200.3, R136.2, U23.6
QST23: JP209.3, R142.2, U24.6
QST24: JP218.3, R148.2, U25.6
QST25: JP227.3, R154.2, U26.6
QST26: JP236.3, R160.2, U27.6
QST27: JP245.3, R166.2, U28.6
QST28: JP254.3, R172.2, U29.6
QST29: JP263.3, R178.2, U30.6
QST30: JP272.3, R184.2, U31.6
QST31: JP281.3, R190.2, U32.6
QST32: JP290.3, R196.2, U33.6
QST33: JP299.3, R202.2, U34.6
QST34: JP308.3, R208.2, U35.6
QST35: JP317.3, R214.2, U36.6
QST36: JP326.3, R220.2, U37.6
QST37: JP335.3, R226.2, U38.6
QST38: JP344.3, R232.2, U39.6
QST39: JP353.3, R238.2, U40.6
QST40: JP362.3, R244.2, U41.6
QST41: JP371.3, R250.2, U42.6
QST42: JP380.3, R256.2, U43.6
QST43: JP389.3, R262.2, U44.6
QST44: JP398.3, R268.2, U45.6
QST45: JP407.3, R274.2, U46.6
QST46: JP416.3, R280.2, U47.6
QST47: JP425.3, R286.2, U48.6
QST48: JP434.3, R292.2, U49.6
QST49: JP443.3, R298.2, U50.6
QST50: JP452.3, R304.2, U51.6
QST51: JP461.3, R310.2, U52.6
QST52: JP470.3, R316.2, U53.6
QST53: JP479.3, R322.2, U54.6
QST54: JP488.3, R328.2, U55.6
QST55: JP497.3, R334.2, U56.6
QST56: JP506.3, R340.2, U57.6
QST57: JP515.3, R346.2, U58.6
QST58: JP524.3, R352.2, U59.6
QST59: JP533.3, R358.2, U60.6
QST60: JP542.3, R364.2, U61.6
QST61: JP551.3, R370.2, U62.6
QST62: JP560.3, R376.2, U63.6
QST63: JP569.3, R382.2, U64.6
SCL: JP2.2, R5.1, U2.7
SCL1: JP11.2, R11.1, U1.7
SCL2: JP20.2, R17.1, U3.7
SCL3: JP29.2, R23.1, U4.7
SCL4: JP38.2, R29.1, U5.7
SCL5: JP47.2, R35.1, U6.7
SCL6: JP56.2, R41.1, U7.7
SCL7: JP65.2, R47.1, U8.7
SCL8: JP74.2, R53.1, U9.7
SCL9: JP83.2, R59.1, U10.7
SCL10: JP92.2, R65.1, U11.7
SCL11: JP101.2, R71.1, U12.7
SCL12: JP110.2, R77.1, U13.7
SCL13: JP119.2, R83.1, U14.7
SCL14: JP128.2, R89.1, U15.7
SCL15: JP137.2, R95.1, U16.7
SCL16: JP146.2, R101.1, U17.7
SCL17: JP155.2, R107.1, U18.7
SCL18: JP164.2, R113.1, U19.7
SCL19: JP173.2, R119.1, U20.7
SCL20: JP182.2, R125.1, U21.7
SCL21: JP191.2, R131.1, U22.7
SCL22: JP200.2, R137.1, U23.7
SCL23: JP209.2, R143.1, U24.7
SCL24: JP218.2, R149.1, U25.7
SCL25: JP227.2, R155.1, U26.7
SCL26: JP236.2, R161.1, U27.7
SCL27: JP245.2, R167.1, U28.7
SCL28: JP254.2, R173.1, U29.7
SCL29: JP263.2, R179.1, U30.7
SCL30: JP272.2, R185.1, U31.7
SCL31: JP281.2, R191.1, U32.7
SCL32: JP290.2, R197.1, U33.7
SCL33: JP299.2, R203.1, U34.7
SCL34: JP308.2, R209.1, U35.7
SCL35: JP317.2, R215.1, U36.7
SCL36: JP326.2, R221.1, U37.7
SCL37: JP335.2, R227.1, U38.7
SCL38: JP344.2, R233.1, U39.7
SCL39: JP353.2, R239.1, U40.7
SCL40: JP362.2, R245.1, U41.7
SCL41: JP371.2, R251.1, U42.7
SCL42: JP380.2, R257.1, U43.7
SCL43: JP389.2, R263.1, U44.7
SCL44: JP398.2, R269.1, U45.7
SCL45: JP407.2, R275.1, U46.7
SCL46: JP416.2, R281.1, U47.7
SCL47: JP425.2, R287.1, U48.7
SCL48: JP434.2, R293.1, U49.7
SCL49: JP443.2, R299.1, U50.7
SCL50: JP452.2, R305.1, U51.7
SCL51: JP461.2, R311.1, U52.7
SCL52: JP470.2, R317.1, U53.7
SCL53: JP479.2, R323.1, U54.7
SCL54: JP488.2, R329.1, U55.7
SCL55: JP497.2, R335.1, U56.7
SCL56: JP506.2, R341.1, U57.7
SCL57: JP515.2, R347.1, U58.7
SCL58: JP524.2, R353.1, U59.7
SCL59: JP533.2, R359.1, U60.7
SCL60: JP542.2, R365.1, U61.7
SCL61: JP551.2, R371.1, U62.7
SCL62: JP560.2, R377.1, U63.7
SCL63: JP569.2, R383.1, U64.7
SDA: JP2.1, R6.1, U2.8
SDA1: JP11.1, R12.1, U1.8
SDA2: JP20.1, R18.1, U3.8
SDA3: JP29.1, R24.1, U4.8
SDA4: JP38.1, R30.1, U5.8
SDA5: JP47.1, R36.1, U6.8
SDA6: JP56.1, R42.1, U7.8
SDA7: JP65.1, R48.1, U8.8
SDA8: JP74.1, R54.1, U9.8
SDA9: JP83.1, R60.1, U10.8
SDA10: JP92.1, R66.1, U11.8
SDA11: JP101.1, R72.1, U12.8
SDA12: JP110.1, R78.1, U13.8
SDA13: JP119.1, R84.1, U14.8
SDA14: JP128.1, R90.1, U15.8
SDA15: JP137.1, R96.1, U16.8
SDA16: JP146.1, R102.1, U17.8
SDA17: JP155.1, R108.1, U18.8
SDA18: JP164.1, R114.1, U19.8
SDA19: JP173.1, R120.1, U20.8
SDA20: JP182.1, R126.1, U21.8
SDA21: JP191.1, R132.1, U22.8
SDA22: JP200.1, R138.1, U23.8
SDA23: JP209.1, R144.1, U24.8
SDA24: JP218.1, R150.1, U25.8
SDA25: JP227.1, R156.1, U26.8
SDA26: JP236.1, R162.1, U27.8
SDA27: JP245.1, R168.1, U28.8
SDA28: JP254.1, R174.1, U29.8
SDA29: JP263.1, R180.1, U30.8
SDA30: JP272.1, R186.1, U31.8
SDA31: JP281.1, R192.1, U32.8
SDA32: JP290.1, R198.1, U33.8
SDA33: JP299.1, R204.1, U34.8
SDA34: JP308.1, R210.1, U35.8
SDA35: JP317.1, R216.1, U36.8
SDA36: JP326.1, R222.1, U37.8
SDA37: JP335.1, R228.1, U38.8
SDA38: JP344.1, R234.1, U39.8
SDA39: JP353.1, R240.1, U40.8
SDA40: JP362.1, R246.1, U41.8
SDA41: JP371.1, R252.1, U42.8
SDA42: JP380.1, R258.1, U43.8
SDA43: JP389.1, R264.1, U44.8
SDA44: JP398.1, R270.1, U45.8
SDA45: JP407.1, R276.1, U46.8
SDA46: JP416.1, R282.1, U47.8
SDA47: JP425.1, R288.1, U48.8
SDA48: JP434.1, R294.1, U49.8
SDA49: JP443.1, R300.1, U50.8
SDA50: JP452.1, R306.1, U51.8
SDA51: JP461.1, R312.1, U52.8
SDA52: JP470.1, R318.1, U53.8
SDA53: JP479.1, R324.1, U54.8
SDA54: JP488.1, R330.1, U55.8
SDA55: JP497.1, R336.1, U56.8
SDA56: JP506.1, R342.1, U57.8
SDA57: JP515.1, R348.1, U58.8
SDA58: JP524.1, R354.1, U59.8
SDA59: JP533.1, R360.1, U60.8
SDA60: JP542.1, R366.1, U61.8
SDA61: JP551.1, R372.1, U62.8
SDA62: JP560.1, R378.1, U63.8
SDA63: JP569.1, R384.1, U64.8
VCC: I2C.2, JP4.1, R3.2
VCC1: I2C1.2, JP12.1, R9.2
VCC2: I2C2.2, JP21.1, R15.2
VCC3: I2C3.2, JP30.1, R21.2
VCC4: I2C4.2, JP39.1, R27.2
VCC5: I2C5.2, JP48.1, R33.2
VCC6: I2C6.2, JP57.1, R39.2
VCC7: I2C7.2, JP66.1, R45.2
VCC8: I2C8.2, JP75.1, R51.2
VCC9: I2C9.2, JP84.1, R57.2
VCC10: I2C10.2, JP93.1, R63.2
VCC11: I2C11.2, JP102.1, R69.2
VCC12: I2C12.2, JP111.1, R75.2
VCC13: I2C13.2, JP120.1, R81.2
VCC14: I2C14.2, JP129.1, R87.2
VCC15: I2C15.2, JP138.1, R93.2
VCC16: I2C16.2, JP147.1, R99.2
VCC17: I2C17.2, JP156.1, R105.2
VCC18: I2C18.2, JP165.1, R111.2
VCC19: I2C19.2, JP174.1, R117.2
VCC20: I2C20.2, JP183.1, R123.2
VCC21: I2C21.2, JP192.1, R129.2
VCC22: I2C22.2, JP201.1, R135.2
VCC23: I2C23.2, JP210.1, R141.2
VCC24: I2C24.2, JP219.1, R147.2
VCC25: I2C25.2, JP228.1, R153.2
VCC26: I2C26.2, JP237.1, R159.2
VCC27: I2C27.2, JP246.1, R165.2
VCC28: I2C28.2, JP255.1, R171.2
VCC29: I2C29.2, JP264.1, R177.2
VCC30: I2C30.2, JP273.1, R183.2
VCC31: I2C31.2, JP282.1, R189.2
VCC32: I2C32.2, JP291.1, R195.2
VCC33: I2C33.2, JP300.1, R201.2
VCC34: I2C34.2, JP309.1, R207.2
VCC35: I2C35.2, JP318.1, R213.2
VCC36: I2C36.2, JP327.1, R219.2
VCC37: I2C37.2, JP336.1, R225.2
VCC38: I2C38.2, JP345.1, R231.2
VCC39: I2C39.2, JP354.1, R237.2
VCC40: I2C40.2, JP363.1, R243.2
VCC41: I2C41.2, JP372.1, R249.2
VCC42: I2C42.2, JP381.1, R255.2
VCC43: I2C43.2, JP390.1, R261.2
VCC44: I2C44.2, JP399.1, R267.2
VCC45: I2C45.2, JP408.1, R273.2
VCC46: I2C46.2, JP417.1, R279.2
VCC47: I2C47.2, JP426.1, R285.2
VCC48: I2C48.2, JP435.1, R291.2
VCC49: I2C49.2, JP444.1, R297.2
VCC50: I2C50.2, JP453.1, R303.2
VCC51: I2C51.2, JP462.1, R309.2
VCC52: I2C52.2, JP471.1, R315.2
VCC53: I2C53.2, JP480.1, R321.2
VCC54: I2C54.2, JP489.1, R327.2
VCC55: I2C55.2, JP498.1, R333.2
VCC56: I2C56.2, JP507.1, R339.2
VCC57: I2C57.2, JP516.1, R345.2
VCC58: I2C58.2, JP525.1, R351.2
VCC59: I2C59.2, JP534.1, R357.2
VCC60: I2C60.2, JP543.1, R363.2
VCC61: I2C61.2, JP552.1, R369.2
VCC62: I2C62.2, JP561.1, R375.2
VCC63: I2C63.2, JP570.1, R381.2
VDD: C2.1, R2.1, U2.3
VDD1: C4.1, R8.1, U1.3
VDD2: C6.1, R14.1, U3.3
VDD3: C8.1, R20.1, U4.3
VDD4: C10.1, R26.1, U5.3
VDD5: C12.1, R32.1, U6.3
VDD6: C14.1, R38.1, U7.3
VDD7: C16.1, R44.1, U8.3
VDD8: C18.1, R50.1, U9.3
VDD9: C20.1, R56.1, U10.3
VDD10: C22.1, R62.1, U11.3
VDD11: C24.1, R68.1, U12.3
VDD12: C26.1, R74.1, U13.3
VDD13: C28.1, R80.1, U14.3
VDD14: C30.1, R86.1, U15.3
VDD15: C32.1, R92.1, U16.3
VDD16: C34.1, R98.1, U17.3
VDD17: C36.1, R104.1, U18.3
VDD18: C38.1, R110.1, U19.3
VDD19: C40.1, R116.1, U20.3
VDD20: C42.1, R122.1, U21.3
VDD21: C44.1, R128.1, U22.3
VDD22: C46.1, R134.1, U23.3
VDD23: C48.1, R140.1, U24.3
VDD24: C50.1, R146.1, U25.3
VDD25: C52.1, R152.1, U26.3
VDD26: C54.1, R158.1, U27.3
VDD27: C56.1, R164.1, U28.3
VDD28: C58.1, R170.1, U29.3
VDD29: C60.1, R176.1, U30.3
VDD30: C62.1, R182.1, U31.3
VDD31: C64.1, R188.1, U32.3
VDD32: C66.1, R194.1, U33.3
VDD33: C68.1, R200.1, U34.3
VDD34: C70.1, R206.1, U35.3
VDD35: C72.1, R212.1, U36.3
VDD36: C74.1, R218.1, U37.3
VDD37: C76.1, R224.1, U38.3
VDD38: C78.1, R230.1, U39.3
VDD39: C80.1, R236.1, U40.3
VDD40: C82.1, R242.1, U41.3
VDD41: C84.1, R248.1, U42.3
VDD42: C86.1, R254.1, U43.3
VDD43: C88.1, R260.1, U44.3
VDD44: C90.1, R266.1, U45.3
VDD45: C92.1, R272.1, U46.3
VDD46: C94.1, R278.1, U47.3
VDD47: C96.1, R284.1, U48.3
VDD48: C98.1, R290.1, U49.3
VDD49: C100.1, R296.1, U50.3
VDD50: C102.1, R302.1, U51.3
VDD51: C104.1, R308.1, U52.3
VDD52: C106.1, R314.1, U53.3
VDD53: C108.1, R320.1, U54.3
VDD54: C110.1, R326.1, U55.3
VDD55: C112.1, R332.1, U56.3
VDD56: C114.1, R338.1, U57.3
VDD57: C116.1, R344.1, U58.3
VDD58: C118.1, R350.1, U59.3
VDD59: C120.1, R356.1, U60.3
VDD60: C122.1, R362.1, U61.3
VDD61: C124.1, R368.1, U62.3
VDD62: C126.1, R374.1, U63.3
VDD63: C128.1, R380.1, U64.3
V_BATT: JP1.2, JP5.1, R1.1, R2.2
V_BATT1: JP10.2, JP14.1, R7.1, R8.2
V_BATT2: JP19.2, JP23.1, R13.1, R14.2
V_BATT3: JP28.2, JP32.1, R19.1, R20.2
V_BATT4: JP37.2, JP41.1, R25.1, R26.2
V_BATT5: JP46.2, JP50.1, R31.1, R32.2
V_BATT6: JP55.2, JP59.1, R37.1, R38.2
V_BATT7: JP64.2, JP68.1, R43.1, R44.2
V_BATT8: JP73.2, JP77.1, R49.1, R50.2
V_BATT9: JP82.2, JP86.1, R55.1, R56.2
V_BATT10: JP91.2, JP95.1, R61.1, R62.2
V_BATT11: JP100.2, JP104.1, R67.1, R68.2
V_BATT12: JP109.2, JP113.1, R73.1, R74.2
V_BATT13: JP118.2, JP122.1, R79.1, R80.2
V_BATT14: JP127.2, JP131.1, R85.1, R86.2
V_BATT15: JP136.2, JP140.1, R91.1, R92.2
V_BATT16: JP145.2, JP149.1, R97.1, R98.2
V_BATT17: JP154.2, JP158.1, R103.1, R104.2
V_BATT18: JP163.2, JP167.1, R109.1, R110.2
V_BATT19: JP172.2, JP176.1, R115.1, R116.2
V_BATT20: JP181.2, JP185.1, R121.1, R122.2
V_BATT21: JP190.2, JP194.1, R127.1, R128.2
V_BATT22: JP199.2, JP203.1, R133.1, R134.2
V_BATT23: JP208.2, JP212.1, R139.1, R140.2
V_BATT24: JP217.2, JP221.1, R145.1, R146.2
V_BATT25: JP226.2, JP230.1, R151.1, R152.2
V_BATT26: JP235.2, JP239.1, R157.1, R158.2
V_BATT27: JP244.2, JP248.1, R163.1, R164.2
V_BATT28: JP253.2, JP257.1, R169.1, R170.2
V_BATT29: JP262.2, JP266.1, R175.1, R176.2
V_BATT30: JP271.2, JP275.1, R181.1, R182.2
V_BATT31: JP280.2, JP284.1, R187.1, R188.2
V_BATT32: JP289.2, JP293.1, R193.1, R194.2
V_BATT33: JP298.2, JP302.1, R199.1, R200.2
V_BATT34: JP307.2, JP311.1, R205.1, R206.2
V_BATT35: JP316.2, JP320.1, R211.1, R212.2
V_BATT36: JP325.2, JP329.1, R217.1, R218.2
V_BATT37: JP334.2, JP338.1, R223.1, R224.2
V_BATT38: JP343.2, JP347.1, R229.1, R230.2
V_BATT39: JP352.2, JP356.1, R235.1, R236.2
V_BATT40: JP361.2, JP365.1, R241.1, R242.2
V_BATT41: JP370.2, JP374.1, R247.1, R248.2
V_BATT42: JP379.2, JP383.1, R253.1, R254.2
V_BATT43: JP388.2, JP392.1, R259.1, R260.2
V_BATT44: JP397.2, JP401.1, R265.1, R266.2
V_BATT45: JP406.2, JP410.1, R271.1, R272.2
V_BATT46: JP415.2, JP419.1, R277.1, R278.2
V_BATT47: JP424.2, JP428.1, R283.1, R284.2
V_BATT48: JP433.2, JP437.1, R289.1, R290.2
V_BATT49: JP442.2, JP446.1, R295.1, R296.2
V_BATT50: JP451.2, JP455.1, R301.1, R302.2
V_BATT51: JP460.2, JP464.1, R307.1, R308.2
V_BATT52: JP469.2, JP473.1, R313.1, R314.2
V_BATT53: JP478.2, JP482.1, R319.1, R320.2
V_BATT54: JP487.2, JP491.1, R325.1, R326.2
V_BATT55: JP496.2, JP500.1, R331.1, R332.2
V_BATT56: JP505.2, JP509.1, R337.1, R338.2
V_BATT57: JP514.2, JP518.1, R343.1, R344.2
V_BATT58: JP523.2, JP527.1, R349.1, R350.2
V_BATT59: JP532.2, JP536.1, R355.1, R356.2
V_BATT60: JP541.2, JP545.1, R361.1, R362.2
V_BATT61: JP550.2, JP554.1, R367.1, R368.2
V_BATT62: JP559.2, JP563.1, R373.1, R374.2
V_BATT63: JP568.2, JP572.1, R379.1, R380.2
